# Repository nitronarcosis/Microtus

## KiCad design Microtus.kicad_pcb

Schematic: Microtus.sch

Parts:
C1: 100n; C_0603_1608Metric; LCSC C14663
J1: Conn_01x04; JST_SH_SM04B-SRSS-TB_1x04-1MP_P1.00mm_Horizontal
J2: AVR-ISP-6; PinHeader_2x03_P2.54mm_Vertical
R1: 10k; R_0603_1608Metric; LCSC C25804
R2: 2.49k; R_0603_1608Metric; LCSC C21189
R3: 4.99k; R_0603_1608Metric; LCSC C23046
R4: 1k; R_0603_1608Metric; LCSC C21189
S1: JOYSTICK_THUMB; JOYSTICK
SW1, SW3: SW_Push; Kailh-PG1350-1u-NoLED
SW2: SW_Push; Panasonic_EVQPUL_EVQPUC; LCSC C79174
U1: ATtiny85V-10SU; SOIJ-8_5.3x5.3mm_P1.27mm

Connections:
+3V3: C1.1, J1.2, J2.2, R1.2, R2.2, S1.H1, S1.V1, U1.8 (VCC)
BUTTONS: J2.1, SW1.2, SW3.1, U1.6 (PB1)
GND: C1.2, J1.1, J2.6, R4.1, S1.H3, S1.V3, SW2.2, U1.4 (GND)
I2C_SCL: J1.4, J2.3, U1.7 (PB2)
I2C_SDA: J1.3, J2.4, U1.5 (AREF/PB0)
unnamed: R2.1, R3.2, SW1.1
unnamed: R3.1, R4.2, SW3.2
RESET: J2.5, R1.1, SW2.1, U1.1 (~RESET~/PB5)
X_POS: S1.H2, U1.3 (XTAL2/PB4)
Y_POS: S1.V2, U1.2 (XTAL1/PB3)

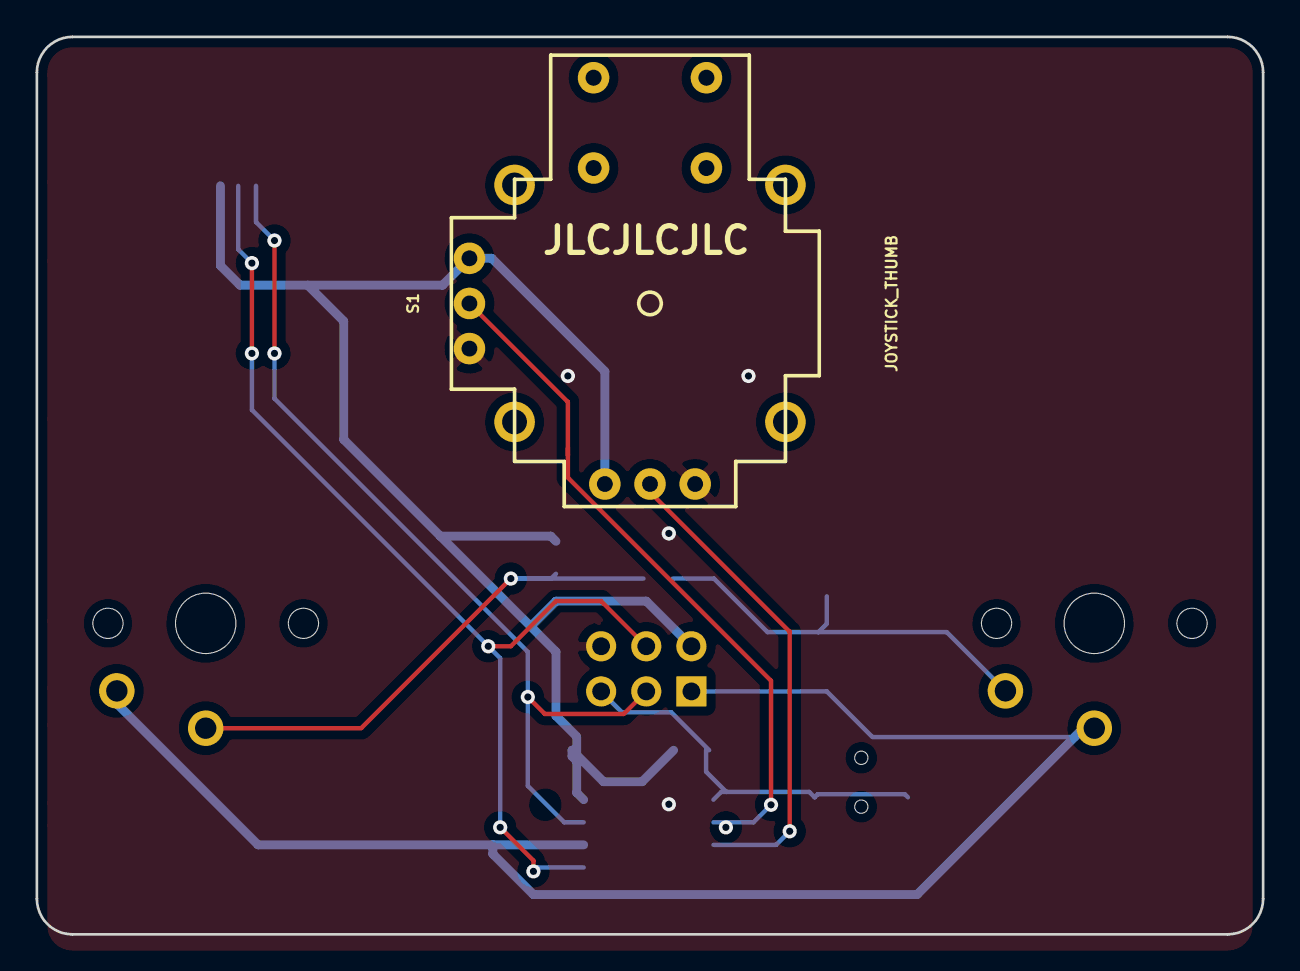
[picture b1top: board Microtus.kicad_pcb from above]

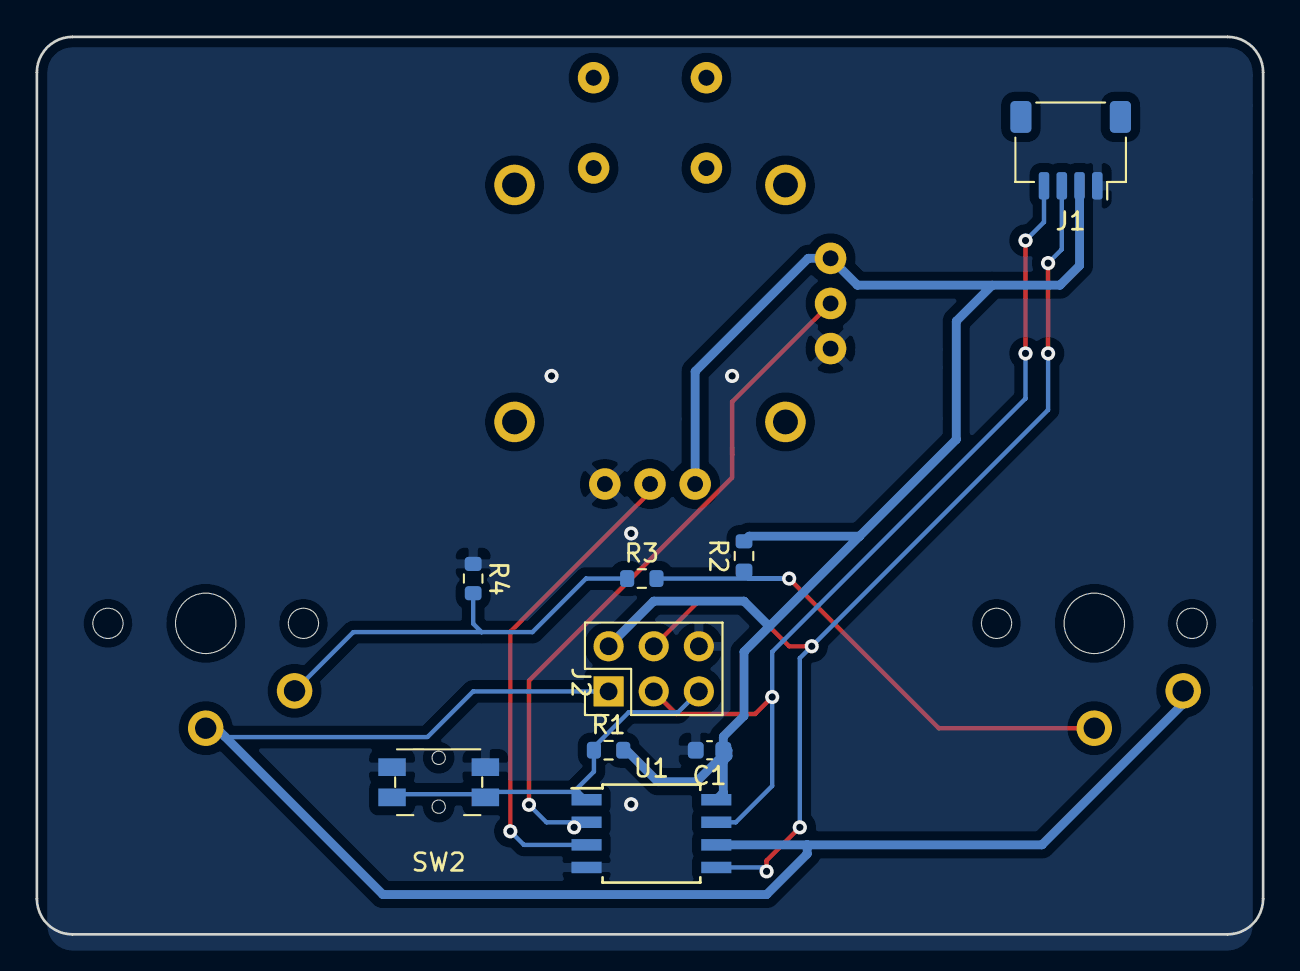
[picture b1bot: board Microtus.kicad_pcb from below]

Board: 2 copper layers, 69.0 x 50.5 mm, 12 parts (9 on the bottom side), 10 nets.

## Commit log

2021-11-25 go with choc switches and 0805 SMDs
2021-11-30 Shrink and switch back to 0603
    also round corners with 2mm radius
2021-12-04 Add STEP files for better rendering
